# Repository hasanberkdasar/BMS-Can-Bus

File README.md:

#  Smart BMS (BQ76952 & STM32F103) — 4S Lithium Battery Management System

##  About The Project & Personal Context
This project is an open-source **4S Smart Battery Management System (BMS)** designed around the **Texas Instruments BQ76952** Analog Front-End (AFE) and an **STM32F103C8T6** microcontroller. 

As a **1st-year Electrical and Electronics Engineering student**, this project represents my very first custom PCB design experience. It was built purely as a personal prototype, a learning step, and a hands-on exploration of power electronics and embedded hardware design. Because of my beginner level, the schematic and layout might appear complex, unoptimized, or messy in certain areas—it was developed as a continuous trial-and-error learning path.

---

## ⚠️ Important Engineering Note: Scaling Down from 100A to 5A

* **Original Scope vs. Current Reality:** The initial goal was to build a high-power 100A continuous BMS. However, as the design progressed, I realized that managing thermal dissipation and routing high-current copper paths properly on a standard 2-layer PCB exceeded my current technical expertise. 
* **Current Power Rating:** To keep the design safe and realistic, the continuous current rating has been officially scaled down to **5A continuous (15A peak)** for this version.
* **Why Some Traces Look Unusually Large:** You will notice that certain power paths on the board are disproportionately wide for a 5A system. These are remnants of the original 100A power path layout attempts.
* **Tested Status:** Please note that **this design has NOT been physically fabricated or hardware-tested**. It exists purely as a CAD/EDA design file.
* **Future Outlook:** The project is temporarily put on hold. Once I gain further engineering experience and technical proficiency, I plan to revisit this project to optimize thermal management and push the layout to support 100A peak and 50–60A continuous power on a computer simulation environment.

---

##  Architecture & Component Selection

### 1. Topology Selection (4S System)
A 4-series (4S) Lithium-ion / LiFePO4 configuration was selected as it matches standard low-voltage applications (such as 12V system upgrades, small EVs, or robotics power distribution) while offering a safe voltage range for learning.

### 2. Key Components & Selection Rationale
* **Texas Instruments BQ76952 (AFE):** Chosen for its highly integrated cell monitoring, hardware-level overvoltage/undervoltage protection, and flexible low-side/high-side FET drive capabilities.
* **STM32F103C8T6 (MCU):** Used as the primary host controller to read telemetry data via I2C/SMBus from the BQ76952, execute custom BMS logic, and manage external communications.
* **SN65HVD230 (CAN Transceiver):** Selected to convert the MCU's UART/CAN signals into a robust differential CAN-bus signal, making the BMS compatible with industrial and automotive telemetry networks.
* **NTC Thermistors:** External thermistor headers are added for real-time thermal monitoring of the battery pack and power MOSFETs.

---

##  Circuit Interconnections & Features

* **Power Path:** Utilizes dual-layer 2mm copper traces with a high-side back-to-back MOSFET pair (paralleled discharge/charge FETs) for battery isolation, and a low-side shunt resistor for current sensing.
* **Noise Immunity & Layout:** Decoupling capacitors are placed in immediate proximity to the power pins of both the AFE and MCU. The 8MHz crystal load capacitors are locked close to the oscillator pins.
* **EMC Shielding:** Top and bottom layers are encased with a solid Ground (GND) polygon pour for noise suppression.
* **Communication Interface:** Dedicated CAN-Bus interface pins enable continuous telemetry streaming (cell voltages, pack current, temperatures, and fault flags) to external dashboards or vehicle control units (VCU).

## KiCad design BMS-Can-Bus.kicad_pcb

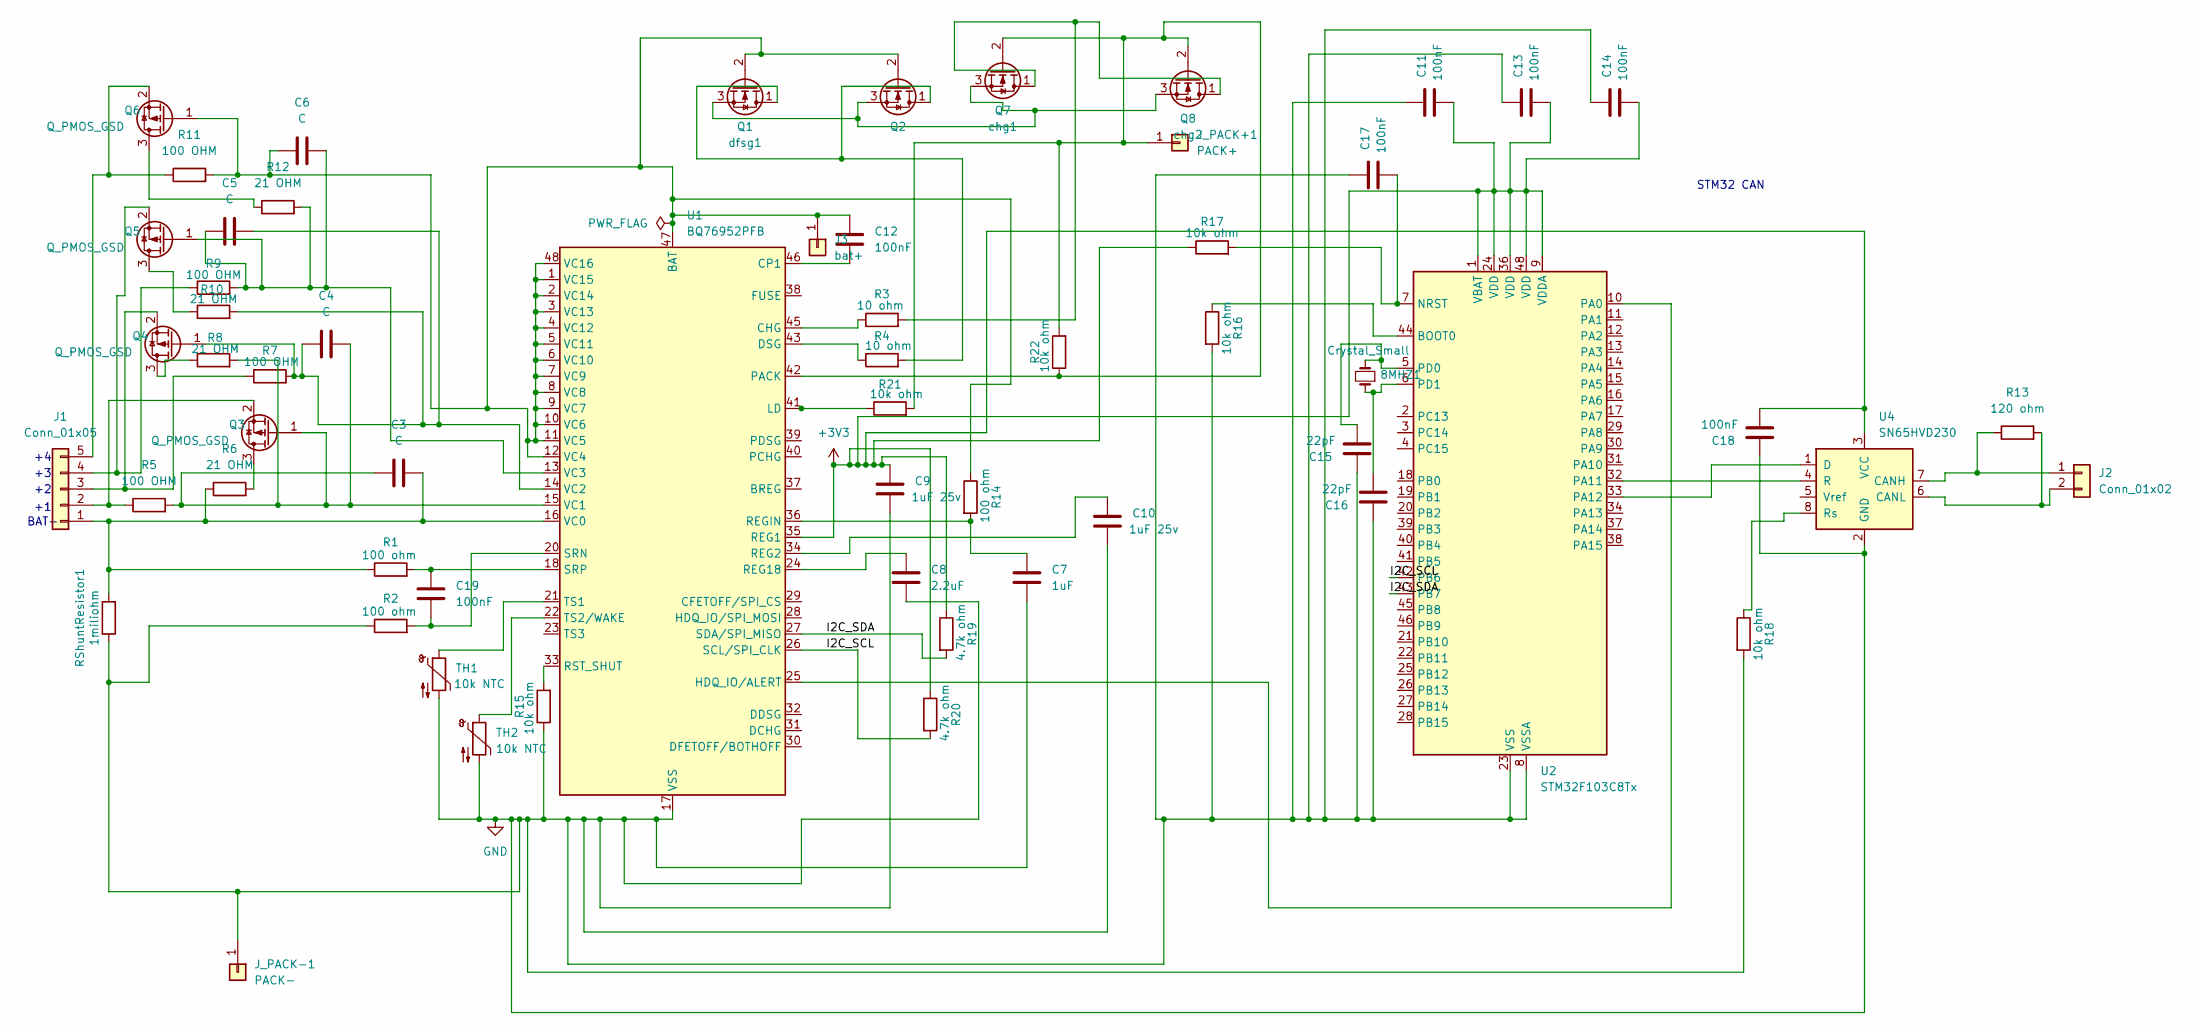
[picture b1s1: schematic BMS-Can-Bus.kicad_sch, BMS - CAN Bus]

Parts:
8MHZ1: Crystal_Small; Crystal_HC49-4H_Vertical
C3, C4, C5, C6: C; C_0603_1608Metric
C7: 1uF; C_0603_1608Metric
C8: 2.2uF; C_0603_1608Metric
C9, C10: 1uF 25v; C_0603_1608Metric
C11, C12, C13, C14, C17, C18, C19: 100nF; C_0603_1608Metric
C15, C16: 22pF; C_0603_1608Metric
J1: Conn_01x05; PinHeader_1x05_P2.54mm_Vertical
J2: Conn_01x02; PinHeader_1x02_P2.54mm_Vertical
J3: bat+; MountingHole_3.2mm_M3_Pad
J_PACK+1: PACK+; MountingHole_5.3mm_M5_Pad
J_PACK-1: PACK-; MountingHole_5.3mm_M5_Pad
Q1: dfsg1; TO-263-2
Q2: dsg2; TO-263-2
Q3, Q4, Q5, Q6: Q_PMOS_GSD; TO-220-3_Vertical
Q7: chg1; TO-263-2
Q8: chg2; TO-263-2
R1, R2, R14: 100 ohm; R_0805_2012Metric
R3, R4: 10 ohm; R_0805_2012Metric
R5, R7, R9, R11: 100 OHM; R_0603_1608Metric
R6, R8, R10, R12: 21 OHM; R_2512_6332Metric
R13: 120 ohm; R_0805_2012Metric
R15, R16, R17, R18, R21, R22: 10k ohm; R_0805_2012Metric
R19, R20: 4.7k ohm; R_0805_2012Metric
RShuntResistor1: 1miliohm; R_Axial_DIN0414_L11.9mm_D4.5mm_P25.40mm_Horizontal
TH1, TH2: 10k NTC; PinHeader_1x02_P2.54mm_Vertical
U1: BQ76952PFB; TQFP-48_7x7mm_P0.5mm
U2: STM32F103C8Tx; LQFP-48_7x7mm_P0.5mm
U4: SN65HVD230; SOIC-8_3.9x4.9mm_P1.27mm

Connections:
+3V3: C9.2, C11.1, C13.1, C14.1, C18.1, R17.1, R19.1, R20.1, U1.35 (REG1), U2.1 (VBAT), U2.9 (VDDA), U2.24 (VDD), U2.36 (VDD), U2.48 (VDD), U4.3 (VCC)
/I2C_SCL: R20.2, U1.26 (SCL/SPI_CLK), U2.42 (PB6)
/I2C_SDA: R19.2, U1.27 (SDA/SPI_MISO), U2.43 (PB7)
GND: C7.1, C8.1, C9.1, C10.1, C11.2, C13.2, C14.2, C15.2, C16.2, C17.2, C18.2, J_PACK-1.1 (Pin_1_1), R2.1, R15.1, R16.2, R18.2, RShuntResistor1.1, TH1.2, TH2.2, U1.17 (VSS), U2.8 (VSSA), U2.23 (VSS), U2.35 (VSS), U2.47 (VSS), U4.2 (GND)
unnamed: C3.2, J1.1, R1.1, R6.1, RShuntResistor1.2, U1.16 (VC0)
unnamed: J1.2, Q3.2 (S), R5.1
unnamed: J1.3, Q4.2 (S), R7.1
unnamed: J1.4, Q5.2 (S), R9.1
unnamed: J1.5, Q6.2 (S), R11.1
unnamed: J2.1, R13.1, U4.7 (CANH)
unnamed: J2.2, R13.2, U4.6 (CANL)
unnamed: C6.1, C12.2, J3.1 (Pin_1_1), Q1.2 (G), Q2.2 (G), Q6.1 (G), R11.2, R14.1, U1.1 (VC15), U1.2 (VC14), U1.3 (VC13), U1.4 (VC12), U1.5 (VC11), U1.6 (VC10), U1.7 (VC9), U1.8 (VC8), U1.9 (VC7), U1.10 (VC6), U1.11 (VC5), U1.12 (VC4), U1.47 (BAT), U1.48 (VC16)
unnamed: J_PACK+1.1 (Pin_1_1), Q7.2 (G), Q8.2 (G), R21.2, R22.1, R22.2, U1.42 (PACK)
unnamed: Q1.1 (D), Q2.1 (D), R4.2
unnamed: Q1.3 (S), Q2.3 (S), Q7.3 (S), Q8.3 (S)
unnamed: Q3.3 (D), R6.2
unnamed: C3.1, C4.2, Q3.1 (G), R5.2, R8.2, U1.15 (VC1)
unnamed: Q4.3 (D), R8.1
unnamed: C4.1, C5.2, Q4.1 (G), R7.2, R10.2, U1.14 (VC2)
unnamed: Q5.3 (D), R10.1
unnamed: C5.1, C6.2, Q5.1 (G), R9.2, R12.2, U1.13 (VC3)
unnamed: Q6.3 (D), R12.1
unnamed: Q7.1 (D), Q8.1 (D), R3.2
unnamed: R3.1, U1.45 (CHG)
unnamed: C12.1, U1.46 (CP1)
unnamed: R4.1, U1.43 (DSG)
unnamed: U1.25 (HDQ_IO/ALERT), U2.10 (PA0)
unnamed: R21.1, U1.41 (LD)
unnamed: C10.2, U1.34 (REG2)
unnamed: C8.2, U1.24 (REG18)
unnamed: C7.2, R14.2, U1.36 (REGIN)
unnamed: R15.2, U1.33 (RST_SHUT)
unnamed: C19.1, R2.2, U1.20 (SRN)
unnamed: C19.2, R1.2, U1.18 (SRP)
unnamed: TH1.1, U1.21 (TS1)
unnamed: TH2.1, U1.22 (TS2/WAKE)
unnamed: R16.1, U2.44 (BOOT0)
unnamed: C17.1, R17.2, U2.7 (NRST)
unnamed: U2.32 (PA11), U4.4 (R)
unnamed: U2.33 (PA12), U4.1 (D)
unnamed: 8MHZ1.2, C15.1, U2.5 (PD0)
unnamed: 8MHZ1.1, C16.1, U2.6 (PD1)
unnamed: R18.1, U4.8 (Rs)

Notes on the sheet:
STM32 CAN
BAT-

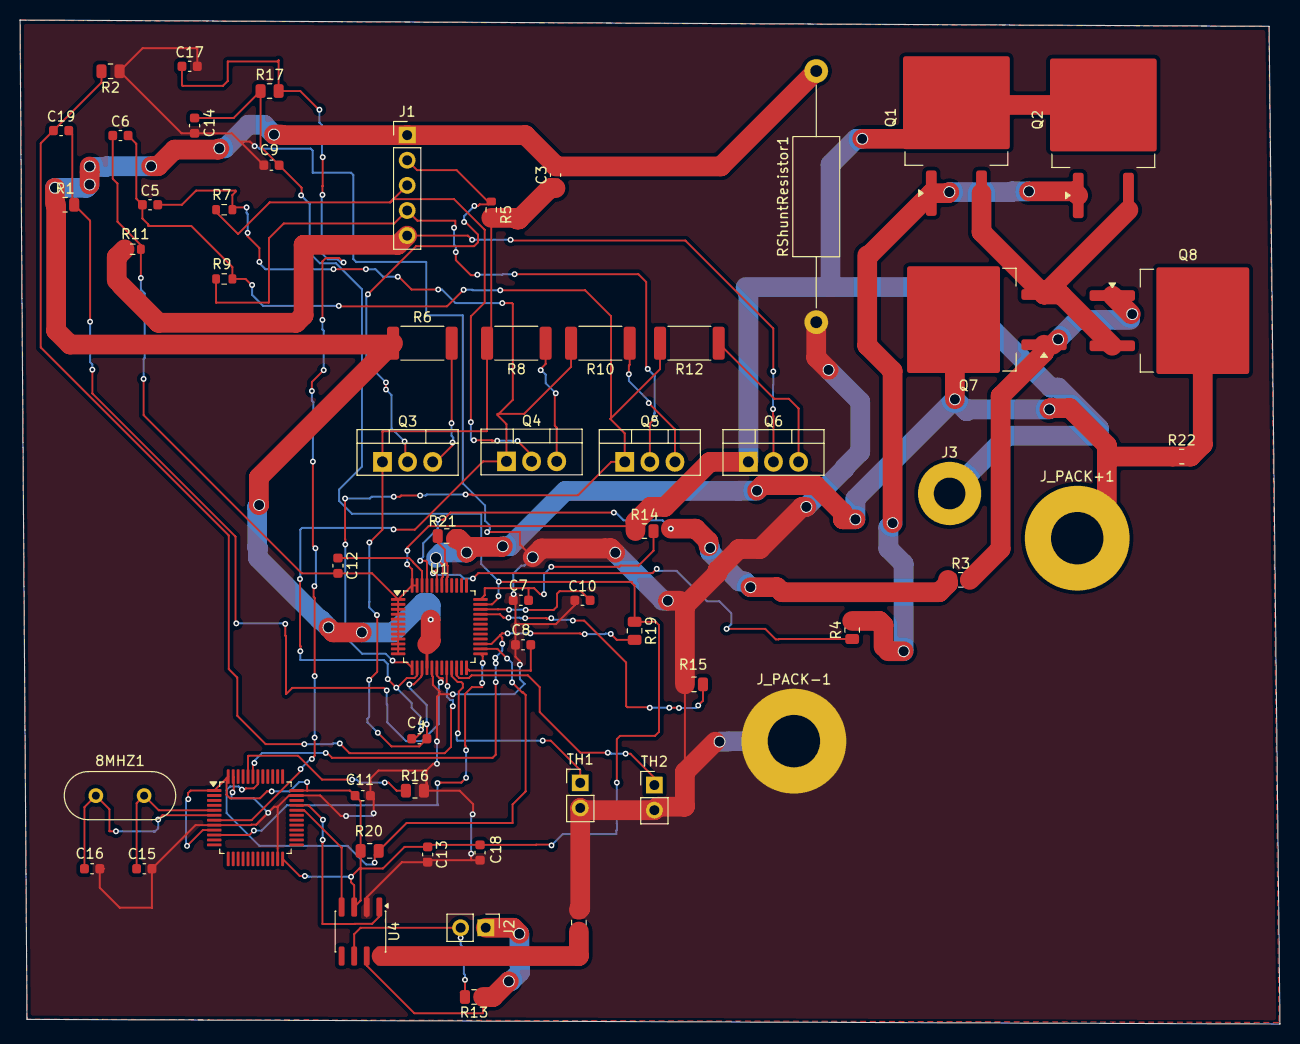
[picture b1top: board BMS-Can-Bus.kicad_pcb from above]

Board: 2 copper layers, 127.4 x 101.5 mm, 59 parts (0 on the bottom side), 43 nets.
